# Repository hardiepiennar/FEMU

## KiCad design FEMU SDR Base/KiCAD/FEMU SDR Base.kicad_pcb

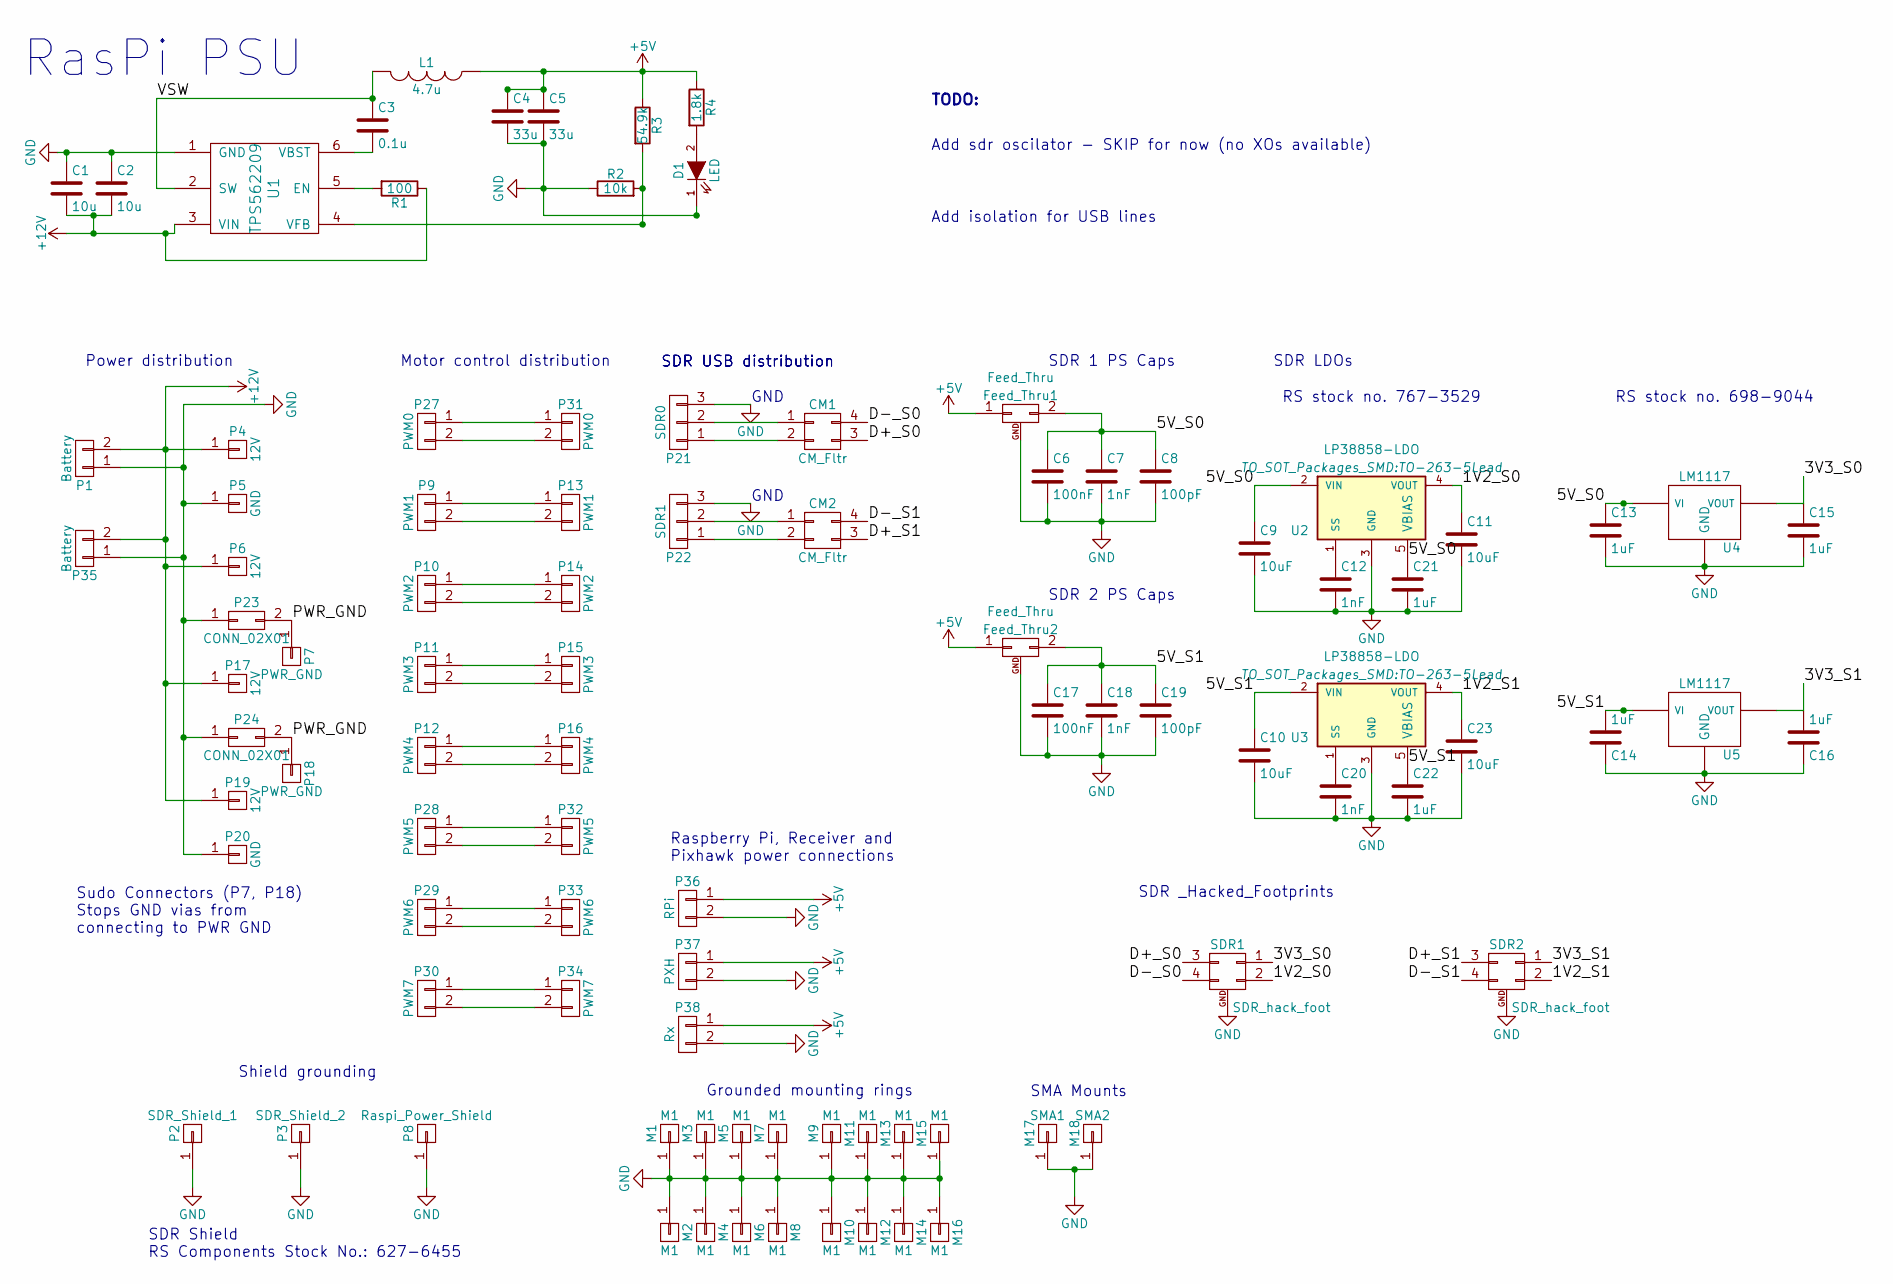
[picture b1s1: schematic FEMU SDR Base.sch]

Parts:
C1, C2: 10u; C_0805_HandSoldering
C3: 0.1u; C_0805_HandSoldering
C4, C5: 33u; TantalC_SizeS_EIA-3216
C6, C17: 100nF; C_0805_HandSoldering
C7, C18: 1nF; C_0805_HandSoldering
C8, C19: 100pF; C_0805_HandSoldering
C9, C10, C11, C23: 10uF; C_0603_HandSoldering
C12, C20: 1nF; C_0603_HandSoldering
C13, C14, C15, C16, C21, C22: 1uF; C_0603_HandSoldering
CM1, CM2: CM_Fltr; TDK_ACM_CM_filter
D1: LED; LED_0805
Feed_Thru1, Feed_Thru2: Feed_Thru; AVX_W#F_FeedThrough_SMD_Caps
L1: 4.7u; L_Wurth_74404052039
M1, M2, M3, M4, M5, M6, M7, M8, M9, M10, M11, M12, M13, M14, M15, M16: M1; MountHole
M17: SMA1; MountHole
M18: SMA2; MountHole
P1, P35: Battery; XT60
P2: SDR_Shield_1; SDR_Shield_75x50mm
P3: SDR_Shield_2; SDR_Shield_75x50mm
P4, P6, P17, P19: 12V; 1Pin
P5, P20: GND; 1Pin
P7, P18: PWR_GND; 1Pin
P8: Raspi_Power_Shield; PCB_Shield_26x16mm
P9, P13: PWM1; SMD-1206_Pol
P10, P14: PWM2; SMD-1206_Pol
P11, P15: PWM3; SMD-1206_Pol
P12, P16: PWM4; SMD-1206_Pol
P21: SDR0; USB
P22: SDR1; USB
P23, P24: CONN_02X01; Conn_PWR_GND_to_GND
P27, P31: PWM0; SMD-1206_Pol
P28, P32: PWM5; SMD-1206_Pol
P29, P33: PWM6; SMD-1206_Pol
P30, P34: PWM7; SMD-1206_Pol
P36: RPi; SMD-1206_Pol
P37: PXH; SMD-1206_Pol
P38: Rx; SMD-1206_Pol
R1: 100; R_0603_HandSoldering
R2: 10k; R_0603_HandSoldering
R3: 54.9k; R_0805_HandSoldering
R4: 1.8k; C_0805_HandSoldering
SDR1, SDR2: SDR_hack_foot; SDR_hack_outline
U1: TPS562209
U2, U3: LP38858-LDO; TO-263-5Lead
U4, U5: LM1117; TO-252-2Lead

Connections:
+5V: C4.1, C5.1, Feed_Thru1.1, Feed_Thru2.1, L1.1, P36.1, P37.1, P38.1, R3.1, R4.1
+12V: C1.2, C2.2, P1.2, P4.1, P6.1, P17.1, P19.1, P35.2, R1.1, U1.3 (VIN)
/1V2_S0: C11.1, SDR1.2, U2.4 (VOUT)
/1V2_S1: C23.1, SDR2.2, U3.4 (VOUT)
/3V3_S0: C15.1, SDR1.1, U4.3 (VOUT)
/3V3_S1: C16.2, SDR2.1, U5.3 (VOUT)
/5V_S0: C6.1, C7.1, C8.1, C9.1, C13.1, C21.1, Feed_Thru1.2, U2.2 (VIN), U2.5 (VBIAS), U4.1 (VI)
/5V_S1: C10.1, C14.2, C17.1, C18.1, C19.1, C22.1, Feed_Thru2.2, U3.2 (VIN), U3.5 (VBIAS), U5.1 (VI)
/D+_S0: CM1.3 (P4), SDR1.3
/D+_S1: CM2.3 (P4), SDR2.3
/D-_S0: CM1.4 (P2), SDR1.4
/D-_S1: CM2.4 (P2), SDR2.4
/PWR_GND: P7.1, P18.1, P23.2, P24.2, P24.PWR_
/VSW: C3.1, L1.2, U1.2 (SW)
GND: C1.1, C2.1, C4.2, C5.2, C6.2, C7.2, C8.2, C9.2, C10.2, C11.2, C12.2, C13.2, C14.1, C15.2, C16.1, C17.2, C18.2, C19.2, C20.2, C21.2, C22.2, C23.2, D1.1 (K), Feed_Thru1.GND, Feed_Thru2.GND, M1.1, M2.1, M3.1, M4.1, M5.1, M6.1, M7.1, M8.1, M9.1, M10.1, M11.1, M12.1, M13.1, M14.1, M15.1, M16.1, M17.1, M18.1, P1.1, P2.1, P3.1, P5.1, P8.1, P20.1, P21.3, P22.3, P23.1, P23.GND, P24.1, P24.GND, P35.1, P36.2, P37.2, P38.2, R2.1, SDR1.GND, SDR2.GND, U1.1 (GND), U2.3 (GND), U3.3 (GND), U4.2 (GND), U5.2 (GND)
unnamed: C3.2, U1.6 (VBST)
unnamed: C12.1, U2.1 (SS)
unnamed: C20.1, U3.1 (SS)
unnamed: CM1.1, P21.2
unnamed: CM1.2 (P3), P21.1
unnamed: CM2.1, P22.2
unnamed: CM2.2 (P3), P22.1
unnamed: D1.2 (A), R4.2
unnamed: P10.1, P14.1
unnamed: P10.2, P14.2
unnamed: P11.1, P15.1
unnamed: P11.2, P15.2
unnamed: P12.1, P16.1
unnamed: P12.2, P16.2
unnamed: P9.1, P13.1
unnamed: P9.2, P13.2
unnamed: P27.1, P31.1
unnamed: P27.2, P31.2
unnamed: P28.1, P32.1
unnamed: P28.2, P32.2
unnamed: P29.1, P33.1
unnamed: P29.2, P33.2
unnamed: P30.1, P34.1
unnamed: P30.2, P34.2
unnamed: R1.2, U1.5 (EN)
unnamed: R2.2, R3.2, U1.4 (VFB)

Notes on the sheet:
RasPi PSU
Power distribution
Motor control distribution
Shield grounding
Add sdr oscilator - SKIP for now (no XOs available)
Add isolation for USB lines
TODO:
SDR 1 PS Caps
RS stock no. 767-3529
RS stock no. 698-9044
SDR LDOs
SDR 2 PS Caps
SDR Shield RS Components Stock No.: 627-6455
Grounded mounting rings
Raspberry Pi, Receiver and Pixhawk power connections
SDR USB distribution
GND
SDR _Hacked_Footprints
SMA Mounts
Sudo Connectors (P7, P18) Stops GND vias from connecting to PWR GND

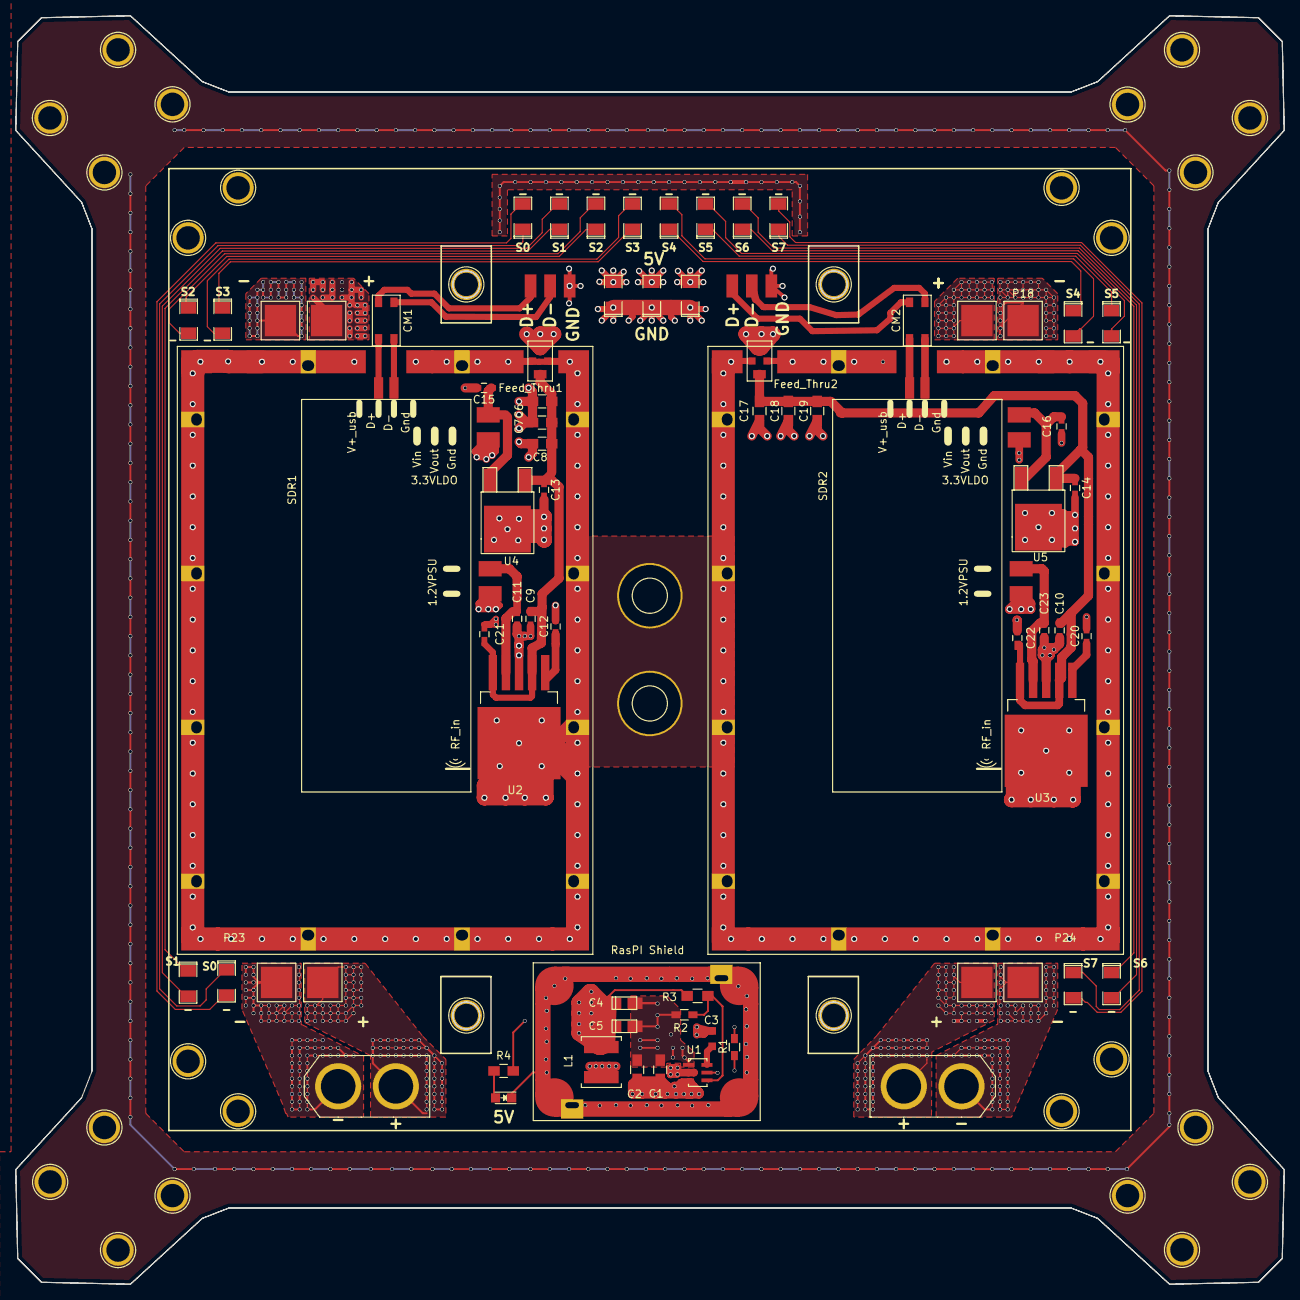
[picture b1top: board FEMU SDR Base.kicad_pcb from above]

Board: 4 copper layers, 164.8 x 164.8 mm, 94 parts (0 on the bottom side), 41 nets.

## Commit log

2016-04-04 Initial commit, added dxf file for base shape.
2016-04-04 Added outline and shield drawings
2016-04-05 PSU for RaspPi added in schematic, lib and footprint added for PSU IC (TPS562209) - these local lib files are now included
2016-04-07 Added text file to monitor work on this repo and avoid losing work due
2016-04-07 Changed status to free
2016-04-08 Changed status to BUSY
2016-04-08 STATUS changed to FREE; Footprint ascociations added
2016-04-12 STATUS = FREE ; pcbnew layout of RasPi PSU added, Changed to 4 layers.
2016-04-13 STATUS=FREE
2016-04-28 Started populating schematic
2016-05-03 STATUS = BUSY - working on SDR mods
2016-05-03 added footprints and some elements to netlist
2016-05-03 STATUS == FREE
2016-05-04 added SDR LDO components and edited RasPi PSU shield footprint
2016-05-05 Base schematic edit
2016-05-05 STATUS==BUSY
2016-05-05 Added SDR shield footprint, updated raspi shield footprints
2016-05-10 STATUS=FREE, shifted one sdr footprint
2016-05-10 rearranged components in SDR shield footrpint
2016-05-10 STATUS=BUSY
2016-05-10 added hacked SDR outline
2016-05-10 Planning and review
2016-05-11 Changed statys
2016-05-11 Added keepout zones for mechanical structures
2016-05-11 Changed status
2016-05-11 Status changed to BUSY
2016-05-11 STATUS = FREE, RASPI PSU smaller layout, footprints swapped
2016-05-12 Added pads for power, usb and pwm distribution
2016-05-12 STATUS=FREE, RasPi Power fit in
2016-05-13 Routed PWM wires and via stitched esc pads -3 hours of work...
2016-05-13 STATUS=FREE, Redo of RaspiPSU to avoid zone errors, trace start for +5V
2016-05-13 Busy
2016-05-13 Added gasket grounding
2016-05-14 Added power connections, power routing, GND isolation and cable tray grounding
2016-05-14 Added esc mounts, power headers and usb headers
2016-05-14 Added Stitching to RasPi PSU and finished this layout, added feedthrough and CM filter foots
2016-05-14 STATUS=FREE, SDR1 arranged
2016-05-14 Moved 5V power lines and moved drawings to silkscreen layer
2016-05-14 added MPS logo to footprints / Misc_footprints
2016-05-14 SDR2 populated
2016-05-15 Changed state
2016-05-15 Added back silkscreen, fixed issues and added mounting holes
2016-05-15 Free
2016-05-15 Last Tasks: Moved SDR pads away from shields, layouts refined, added FMask pads to traces for continuous shield contact, added MPS LOGO... Final checks TODO
2016-05-19 Status=Free, Ground -12V overlap fixed on power pins, stitching vias made smaller to stay within Seeed manufacturing limits, cable tray vias all connected to ground, bottom silkscreen overlap of text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
2016-05-20 saving progress while separating GND and PWR GND vias
2016-05-21 Disconnected VIA connections from GND (layer2) onto PWR_GND current zones for motor return. Added sudo pads in Schematic to allow the GND and PWR_GND nets to connect
2016-05-21 Fixed accidentally deleted connection of far-side battery connector
2016-05-21 Pre-fab version
2016-05-21 Moved MPS logo
2016-05-21 Adjusted some Slikscreen entries
2016-06-14 Fabrication fix
